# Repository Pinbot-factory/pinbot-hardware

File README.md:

**Pinbot** is an open-source platform for quickly building test jigs for electronics QA. The platform is made up of mechanical fixtures, control electronics, jig-level software and backend to store all test results.

**This repo is in active development. New HW will be released soon.**

## Pinbot Hardware
This repo is dedicated for electronics of a typical Pinbot jig. Now it is a compact carrier board for Raspberry Pi 0.

**It features:**
- 8 channels ADC 0-24V
- 8 channels GPIO 0-24V
- 4 signal relays
- USB hub (4x, with power control)
- Qwiic connector for I2C
- USB-C for power supply

Carrier board is 150x30mm. Repo includes KiCAD source files, generated gerbers, BOM, and everything to produce it on your own.

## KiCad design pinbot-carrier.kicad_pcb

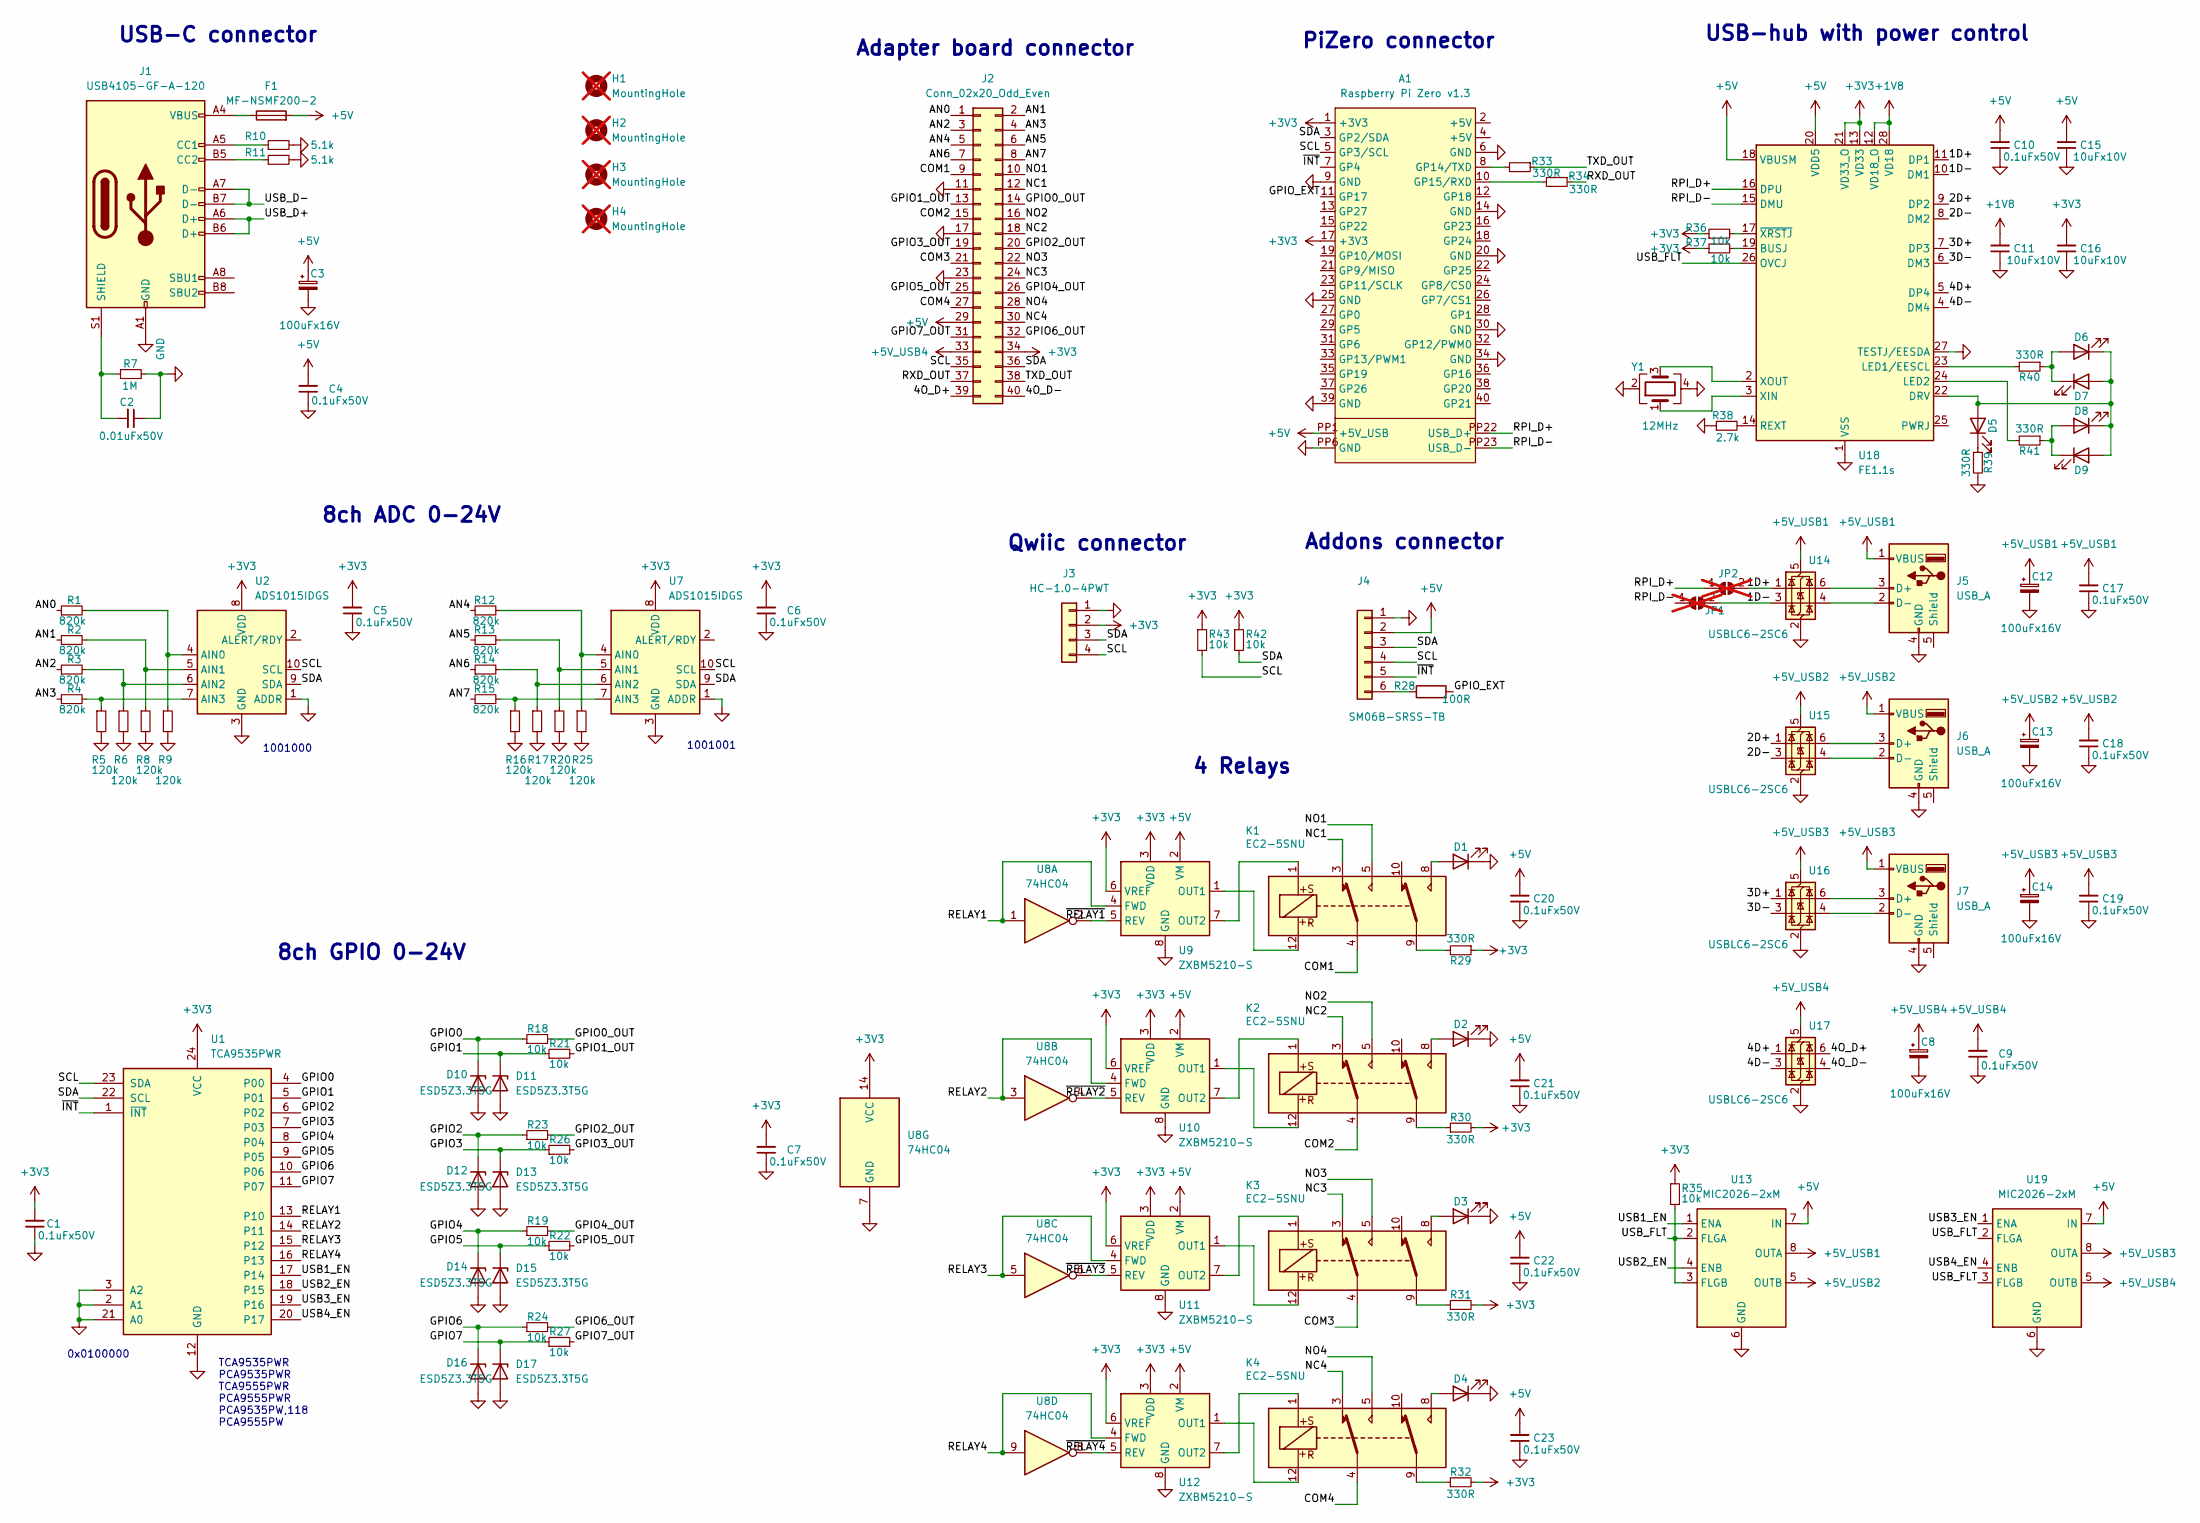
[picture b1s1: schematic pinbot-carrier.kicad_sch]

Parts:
A1: Raspberry Pi Zero v1.3; RASPI_ZERO_FULL
C1: 0.1uFx50V; C_0603_1608Metric; Mouser Part # CGA3E2X7R1H104M080AA
C2: 0.01uFx50V; C_0603_1608Metric; Mouser Part # 06031C103K4T4A; LCSC Part # C100042
C3, C8, C12, C13, C14: 100uFx16V; CP_Elec_6.3x5.4; Mouser Part # UWT1C101MCL1GB; LCSC Part # C129250
C4, C5, C6, C7, C9, C10, C17, C18, C19, C20, C21, C22, C23: 0.1uFx50V; C_0603_1608Metric; Mouser Part # CGA3E2X7R1H104M080AA; LCSC Part # C282519
C11, C15, C16: 10uFx10V; C_0603_1608Metric; Mouser Part # GRM188Z71A106MA73J; LCSC Part # C2959727
D1, D2, D3, D4, D6, D7, D8, D9: LTST-S270KGKT; LED_0603_1608Metric_side; Mouser Part # LTST-S270KGKT; LCSC Part # C125113
D5: LTST-S270KRKT; LED_0603_1608Metric_side; Mouser Part # LTST-S270KRKT; LCSC Part # C125114
D10, D11, D12, D13, D14, D15, D16, D17: ESD5Z3.3T5G; D_SOD-523; Mouser Part # ESD5Z3.3T5G
F1: MF-NSMF200-2; Fuse_1206_3216Metric; Mouser Part # MF-NSMF200-2; LCSC Part # C89656
H1, H2, H3, H4: MountingHole; MountingHole_3.2mm_M3_keepouts; not fitted
J1: USB4105-GF-A-120; USB_C_Receptacle_GCT_USB4105-xx-A_16P_TopMnt_Horizontal; Mouser Part # USB4105-GF-A-120
J2: Conn_02x20_Odd_Even; PinSocket_2x20_P2.54mm_Vertical; LCSC Part # C2977589
J3: HC-1.0-4PWT; JST_SH_SM04B-SRSS-TB_1x04-1MP_P1.00mm_Horizontal; Mouser Part # 10147606-00004LF; LCSC Part # C2845363
J4: SM06B-SRSS-TB; JST_SM06B-SRSS-TB; Mouser Part # 10147606-00006LF; LCSC Part # C160405
J5, J6, J7: USB_A; GCT_USB1125-GF-B_REVA; Mouser Part # USB1125-GF-B
JP1, JP2: SolderJumper_2_Open; SolderJumper-2_P1.3mm_Open_RoundedPad1.0x1.5mm; not fitted
K1, K2, K3, K4: EC2-5SNU; Relay_DPDT_Kemet_EC2; Mouser Part # EC2-5SNU
R1, R2, R3, R4, R12, R13, R14, R15: 820k; R_0603_1608Metric; Mouser Part # ERJ-3EKF8203V; LCSC Part # C2907070
R5, R6, R8, R9, R16, R17, R20, R25: 120k; R_0603_1608Metric; Mouser Part # CRGCQ0603F120K; LCSC Part # C2930027
R7: 1M; R_0603_1608Metric; Mouser Part # ASC0603-1M0FT5; LCSC Part # C107698
R10, R11: 5.1k; R_0603_1608Metric; Mouser Part # ERJ-3EKF5101V; LCSC Part # C2907114
R18, R19, R21, R22, R23, R24, R26, R27, R35, R36, R37, R42, R43: 10k; R_0603_1608Metric; Mouser Part # RMC1/16K1002DTP; LCSC Part # C2907113
R28: 100R; R_0603_1608Metric; Mouser Part # CRT0603-DY-1000ELF; LCSC Part # C2907089
R29, R30, R31, R32, R33, R34, R39, R40, R41: 330R; R_0603_1608Metric; Mouser Part # RMCF0603FT330R; LCSC Part # C23138
R38: 2.7k; R_0603_1608Metric; Mouser Part # AC0603FR-102K7L; LCSC Part # C13167
U1: TCA9535PWR; TSSOP-24_4.4x7.8mm_P0.65mm; Mouser Part # TCA9535PWR
U2, U7: ADS1015IDGS; TSSOP-10_3x3mm_P0.5mm; Mouser Part # ADS1015IDGS
U8: 74HC04; SOIC-14_3.9x8.7mm_P1.27mm; Mouser Part # 74HC04D,653
U9, U10, U11, U12: ZXBM5210-S; SOIC-8_3.9x4.9mm_P1.27mm; Mouser Part # ZXBM5210-S
U13, U19: MIC2026-2xM; SOIC-8_3.9x4.9mm_P1.27mm; Mouser Part # MIC2026-2YM
U14, U15, U16, U17: USBLC6-2SC6; SOT-23-6; Mouser Part # USBLC6-2SC6
U18: FE1.1s; SSOP-28_3.9x9.9mm_P0.635mm; LCSC Part # C9359
Y1: 12MHz; Crystal_SMD_3225-4Pin_3.2x2.5mm; PartNumber X322512MOB4SI; LCSC Part # C70565

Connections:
+1V8: C11.2, U18.12 (VD18_O), U18.28 (VD18)
+3V3: A1.1 (+3V3), A1.17 (+3V3), C1.2, C5.2, C6.2, C7.2, C16.2, J2.34, J3.2, R29.1, R30.2, R31.2, R32.2, R35.1, R36.1, R37.1, R42.1, R43.1, U1.24 (VCC), U2.8 (VDD), U7.8 (VDD), U8.14 (VCC), U9.3 (VDD), U9.6 (VREF), U10.3 (VDD), U10.6 (VREF), U11.3 (VDD), U11.6 (VREF), U12.3 (VDD), U12.6 (VREF), U18.13 (VD33), U18.21 (VD33_O)
+5V: A1.PP1 (+5V_USB), C3.1, C4.2, C10.2, C15.2, C20.2, C21.2, C22.2, C23.2, F1.2, J2.29, J4.2, U9.2 (VM), U10.2 (VM), U11.2 (VM), U12.2 (VM), U13.7 (IN), U18.18 (VBUSM), U18.20 (VDD5), U19.7 (IN)
+5V_USB1: C12.1, C17.2, J5.1 (VBUS), U13.8 (OUTA), U14.5 (VBUS)
+5V_USB2: C13.1, C18.2, J6.1 (VBUS), U13.5 (OUTB), U15.5 (VBUS)
+5V_USB3: C14.1, C19.2, J7.1 (VBUS), U16.5 (VBUS), U19.8 (OUTA)
+5V_USB4: C8.1, C9.2, J2.33, U17.5 (VBUS), U19.5 (OUTB)
/1D+: JP2.2 (B), U14.1 (I/O1), U18.11 (DP1)
/1D-: JP1.2 (B), U14.3 (I/O2), U18.10 (DM1)
/2D+: U15.1 (I/O1), U18.9 (DP2)
/2D-: U15.3 (I/O2), U18.8 (DM2)
/3D+: U16.1 (I/O1), U18.7 (DP3)
/3D-: U16.3 (I/O2), U18.6 (DM3)
/4D+: U17.1 (I/O1), U18.5 (DP4)
/4D-: U17.3 (I/O2), U18.4 (DM4)
/4O_D+: J2.39, U17.6 (I/O1)
/4O_D-: J2.40, U17.4 (I/O2)
/AN0: J2.1, R1.1
/AN1: J2.2, R2.1
/AN2: J2.3, R3.1
/AN3: J2.4, R4.1
/AN4: J2.5, R12.1
/AN5: J2.6, R13.1
/AN6: J2.7, R14.1
/AN7: J2.8, R15.1
/COM1: J2.9, K1.4
/COM2: J2.15, K2.4
/COM3: J2.21, K3.4
/COM4: J2.27, K4.4
/GPIO0: D10.1 (K), R18.1, U1.4 (P00)
/GPIO0_OUT: J2.14, R18.2
/GPIO1: D11.1 (K), R21.1, U1.5 (P01)
/GPIO1_OUT: J2.13, R21.2
/GPIO2: D12.1 (K), R23.1, U1.6 (P02)
/GPIO2_OUT: J2.20, R23.2
/GPIO3: D13.1 (K), R26.1, U1.7 (P03)
/GPIO3_OUT: J2.19, R26.2
/GPIO4: D14.1 (K), R19.1, U1.8 (P04)
/GPIO4_OUT: J2.26, R19.2
/GPIO5: D15.1 (K), R22.1, U1.9 (P05)
/GPIO5_OUT: J2.25, R22.2
/GPIO6: D16.1 (K), R24.1, U1.10 (P06)
/GPIO6_OUT: J2.32, R24.2
/GPIO7: D17.1 (K), R27.1, U1.11 (P07)
/GPIO7_OUT: J2.31, R27.2
/GPIO_EXT: A1.11 (GP17), R28.2
/NC1: J2.12, K1.3
/NC2: J2.18, K2.3
/NC3: J2.24, K3.3
/NC4: J2.30, K4.3
/NO1: J2.10, K1.5
/NO2: J2.16, K2.5
/NO3: J2.22, K3.5
/NO4: J2.28, K4.5
/RELAY1: U1.13 (P10), U8.1, U9.4 (FWD)
/RELAY2: U1.14 (P11), U8.3, U10.4 (FWD)
/RELAY3: U1.15 (P12), U8.5, U11.4 (FWD)
/RELAY4: U1.16 (P13), U8.9, U12.4 (FWD)
/RPI_D+: A1.PP22 (USB_D+), JP2.1 (A), U18.16 (DPU)
/RPI_D-: A1.PP23 (USB_D-), JP1.1 (A), U18.15 (DMU)
/RXD_OUT: J2.37, R34.1
/SCL: A1.5 (GP3/SCL), J2.35, J3.4, J4.4, R43.2, U1.23 (SDA), U2.10 (SCL), U7.10 (SCL)
/SDA: A1.3 (GP2/SDA), J2.36, J3.3, J4.3, R42.2, U1.22 (SCL), U2.9 (SDA), U7.9 (SDA)
/TXD_OUT: J2.38, R33.1
/USB1_EN: U1.17 (P14), U13.1 (ENA)
/USB2_EN: U1.18 (P15), U13.4 (ENB)
/USB3_EN: U1.19 (P16), U19.1 (ENA)
/USB4_EN: U1.20 (P17), U19.4 (ENB)
/USB_D+: J1.A6 (D+), J1.B6 (D+)
/USB_D-: J1.A7 (D-), J1.B7 (D-)
/USB_FLT: R35.2, U13.2 (FLGA), U13.3 (FLGB), U18.26 (OVCJ), U19.2 (FLGA), U19.3 (FLGB)
/~INT: A1.7 (GP4), J4.5, U1.1 (~INT)
/~RELAY1: U8.2, U9.5 (REV)
/~RELAY2: U8.4, U10.5 (REV)
/~RELAY3: U8.6, U11.5 (REV)
/~RELAY4: U8.8, U12.5 (REV)
GND: A1.6 (GND), A1.9 (GND), A1.14 (GND), A1.20 (GND), A1.25 (GND), A1.30 (GND), A1.34 (GND), A1.39 (GND), A1.PP6 (GND), C1.1, C2.1, C3.2, C4.1, C5.1, C6.1, C7.1, C8.2, C9.1, C10.1, C11.1, C12.2, C13.2, C14.2, C15.1, C16.1, C17.1, C18.1, C19.1, C20.1, C21.1, C22.1, C23.1, D1.1 (K), D2.1 (K), D3.1 (K), D4.1 (K), D10.2 (A), D11.2 (A), D12.2 (A), D13.2 (A), D14.2 (A), D15.2 (A), D16.2 (A), D17.2 (A), J1.A1 (GND), J1.A12 (GND), J1.B1 (GND), J1.B12 (GND), J2.11, J2.17, J2.23, J3.1, J4.1, J5.4 (GND), J6.4 (GND), J7.4 (GND), R5.2, R6.2, R7.2, R8.2, R9.2, R10.2, R11.2, R16.2, R17.2, R20.2, R25.2, R38.1, R39.2, U1.2 (A1), U1.3 (A2), U1.12 (GND), U1.21 (A0), U2.1 (ADDR), U2.3 (GND), U7.1 (ADDR), U7.3 (GND), U8.7 (GND), U9.8 (GND), U10.8 (GND), U11.8 (GND), U12.8 (GND), U13.6 (GND), U14.2 (GND), U15.2 (GND), U16.2 (GND), U17.2 (GND), U18.1 (VSS), U18.27 (TESTJ/EESDA), U19.6 (GND), Y1.2, Y1.4
unnamed: A1.8 (GP14/TXD), R33.2
unnamed: A1.10 (GP15/RXD), R34.2
unnamed: D1.2 (A), K1.8
unnamed: D2.2 (A), K2.8
unnamed: D3.2 (A), K3.8
unnamed: D4.2 (A), K4.8
unnamed: D5.2 (A), D6.1 (K), D7.2 (A), D8.1 (K), D9.2 (A), U18.22 (DRV)
unnamed: D5.1 (K), R39.1
unnamed: D6.2 (A), D7.1 (K), R40.1
unnamed: D8.2 (A), D9.1 (K), R41.1
unnamed: F1.1, J1.A4 (VBUS), J1.A9 (VBUS), J1.B4 (VBUS), J1.B9 (VBUS)
unnamed: J1.A5 (CC1), R10.1
unnamed: J1.B5 (CC2), R11.1
unnamed: C2.2, J1.S1 (SHIELD), R7.1
unnamed: J4.6, R28.1
unnamed: J5.3 (D+), U14.6 (I/O1)
unnamed: J5.2 (D-), U14.4 (I/O2)
unnamed: J6.3 (D+), U15.6 (I/O1)
unnamed: J6.2 (D-), U15.4 (I/O2)
unnamed: J7.3 (D+), U16.6 (I/O1)
unnamed: J7.2 (D-), U16.4 (I/O2)
unnamed: K1.9, R29.2
unnamed: K2.9, R30.1
unnamed: K3.9, R31.1
unnamed: K4.9, R32.1
unnamed: R1.2, R9.1, U2.4 (AIN0)
unnamed: R2.2, R8.1, U2.5 (AIN1)
unnamed: R3.2, R6.1, U2.6 (AIN2)
unnamed: R4.2, R5.1, U2.7 (AIN3)
unnamed: R12.2, R25.1, U7.4 (AIN0)
unnamed: R13.2, R20.1, U7.5 (AIN1)
unnamed: R14.2, R17.1, U7.6 (AIN2)
unnamed: R15.2, R16.1, U7.7 (AIN3)
unnamed: K1.12, U9.1 (OUT1)
unnamed: K1.1, U9.7 (OUT2)
unnamed: K2.12, U10.1 (OUT1)
unnamed: K2.1, U10.7 (OUT2)
unnamed: K3.12, U11.1 (OUT1)
unnamed: K3.1, U11.7 (OUT2)
unnamed: K4.12, U12.1 (OUT1)
unnamed: K4.1, U12.7 (OUT2)
unnamed: R37.2, U18.19 (BUSJ)
unnamed: R40.2, U18.23 (LED1/EESCL)
unnamed: R41.2, U18.24 (LED2)
unnamed: R38.2, U18.14 (REXT)
unnamed: U18.3 (XIN), Y1.1
unnamed: U18.2 (XOUT), Y1.3
unnamed: R36.2, U18.17 (~XRSTJ)

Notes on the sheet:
PiZero connector
USB-C connector
0x0100000
4 Relays
8ch ADC 0-24V
Qwiic connector
1001000
1001001
TCA9535PWR PCA9535PWR TCA9555PWR PCA9555PWR PCA9535PW,118 PCA9555PW
USB-hub with power control
Addons connector
8ch GPIO 0-24V
Adapter board connector

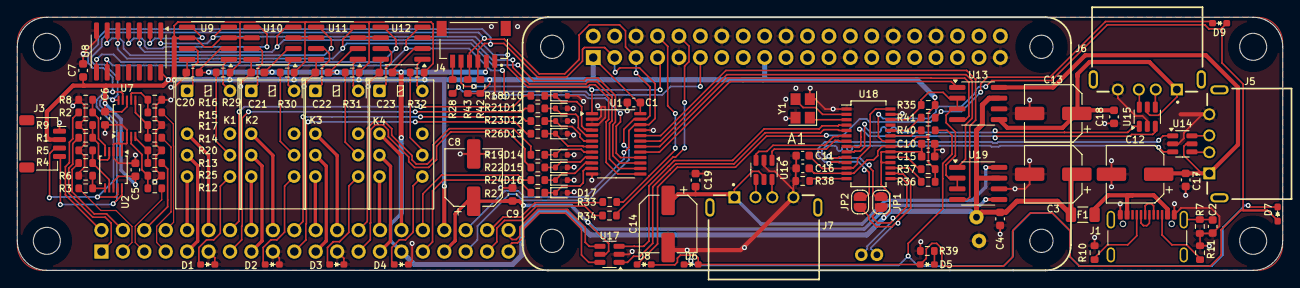
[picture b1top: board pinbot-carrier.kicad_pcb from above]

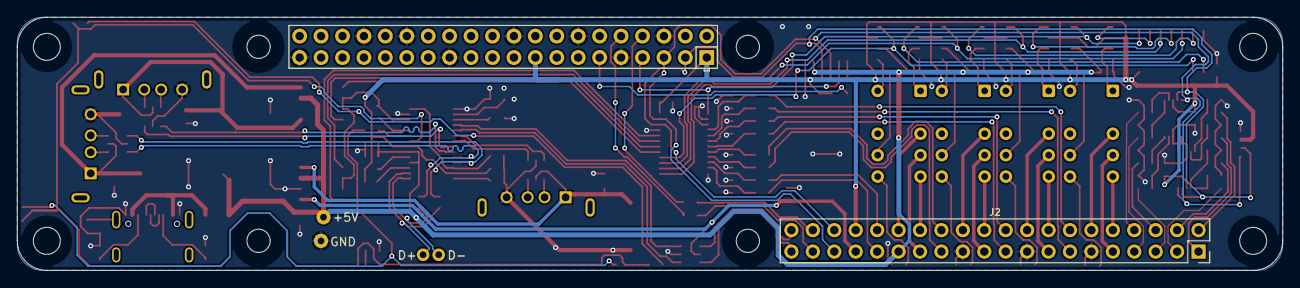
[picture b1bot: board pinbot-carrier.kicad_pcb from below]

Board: 2 copper layers, 150.0 x 30.0 mm, 118 parts (2 on the bottom side), 125 nets.

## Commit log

2025-11-20 readme updated
